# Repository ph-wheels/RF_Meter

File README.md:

# RF_Meter
dual channel rf meter (work in progress)

This project started off with a question concerning replacement or source for
suitable detector diodes for the Boonton RF Millivolt meter quite a few months ago.
As a result of that, the idea was born to create a millivolt and/or power meter
using one of the modern ADC chips available today and since that time a few test
drawning and PCB where used in the process to the current V5 of the ADC board.
This project has been a combined effort with Jacques (ve2azx, http://www.ve2azx.net),
who already had developped a replacement board for the Boonton series of millivolt/
power meter as to fixed the issue with the mechanical chopper, without his valued
contribution, experiance, feedback and high precision RF measurement this project
would never exist.

The current design is based to 2 main PCB's and a battery board which also provides
some shielding to ADC board when mounted on top off it.

The control board consist of a connection to battery board, a flatcable connection
to ADC board and uart connection (ttl level) to external usb serial interface.
The board has and ESP32 MCU chip, which can be flashed via the USB serial interface,
will display info on the LCD screen (3.5" 480x240), monitors changes of the rotary
switch, touch screen, on-board push buttons and read/controls behaviour of the ADC
board. The RF Meter is battery powered and should be capable to provide adequate power
for several hours from 2x 2000 mAh or larger capacity batteries, optional board space
is provided to house a BMS unit and can be charged by the 2S 1A battery charger module
or via a barrel jack socket to deliver power via on-board regulator (3V3) to the MCU and
LCD screen.

The ADC board consist of 2 SMA and a flatcable connection to the control board,
optionally a connection to a 2 pin Amphenol connector, simular to the Boonton instruments.
This board holds 3 main area's being 3x input circuit, multiplexer with the ADC chip and the
voltages / reference sources with some control to switch attenuator and optional panel leds.
The input circuits for channels A/B are terminated with 50 Ohm followed by detector circuit
and attenuator, which is used to obtain a +23dBm range, into a differential low noise x1
amplifier, channel C (with it's components populated) only has the differential 5M6 resistors, the
attenuator and differential low noise x1 amplifier and is therefore not be a 50 Ohm input source.

Project status has been closed for now as we have finished our mean development goals being:
- a battery powered, using modern chips with large enough display making it a usable instrument
- a less than -55 dBm and up to +23 dBm input range
- a frequency range of less then 10 MHz upto in excess of 1 GHz
- an auto range mechanism in place over entire input range
- mechanism in place to load and maintain correction tables in none volatile memory

One area left for improvement is the option to obtain differential power reading between channel
B - A which kind of works (reasonably well within the lower 2 ranges) but will be slower in it's
update frequency then we expected it to be.

Future plans currently don't exist other then having an update schematic in place base on a dual
ADC chip approach which will speedup the channel B - A mode by factor 2x to 3x BUT this will yield
into a higher build cost due to extra ADC and the SSR / Mux chip.

Suggestion as how to build can be found in due time in folder 'Build' which will provide info and
steps to build the ADC and Control board and best practice to test and put each board into operation.

Paul	(PE1FCB (ex))

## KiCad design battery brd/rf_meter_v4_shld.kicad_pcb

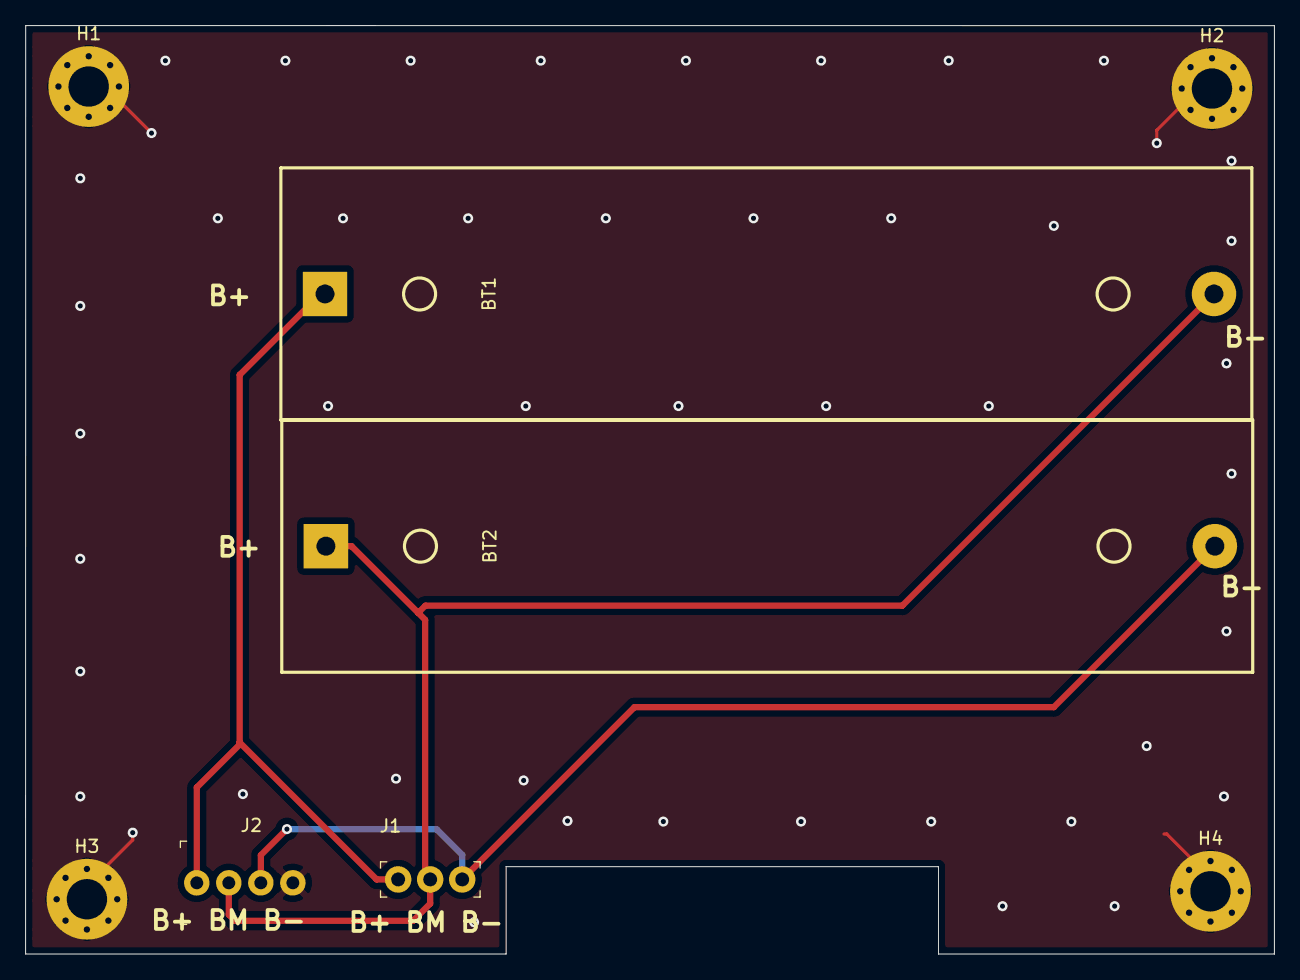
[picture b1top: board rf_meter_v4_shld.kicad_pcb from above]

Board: 2 copper layers, 99.0 x 73.6 mm, 8 parts (0 on the bottom side), 4 nets.

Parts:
BT1, BT2: Li-Ion 18650; Battery_Holder_2S
H1, H2, H3, H4: MountingHole; MountingHole_3.2mm_M3_Pad_Via
J1: Bat_Cntrl; PinHeader_1x3_P2.54_Drill1.1mm
J2: Bat_Test; PinHeader_1x4_P2.54mm_Drill1.02mm

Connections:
GND: H1.1, H2.1, H3.1, H4.1, J2.4
unnamed: BT1.1, J1.1, J2.1
unnamed: BT1.2, BT2.1, J1.2, J2.2
unnamed: BT2.2, J1.3, J2.3

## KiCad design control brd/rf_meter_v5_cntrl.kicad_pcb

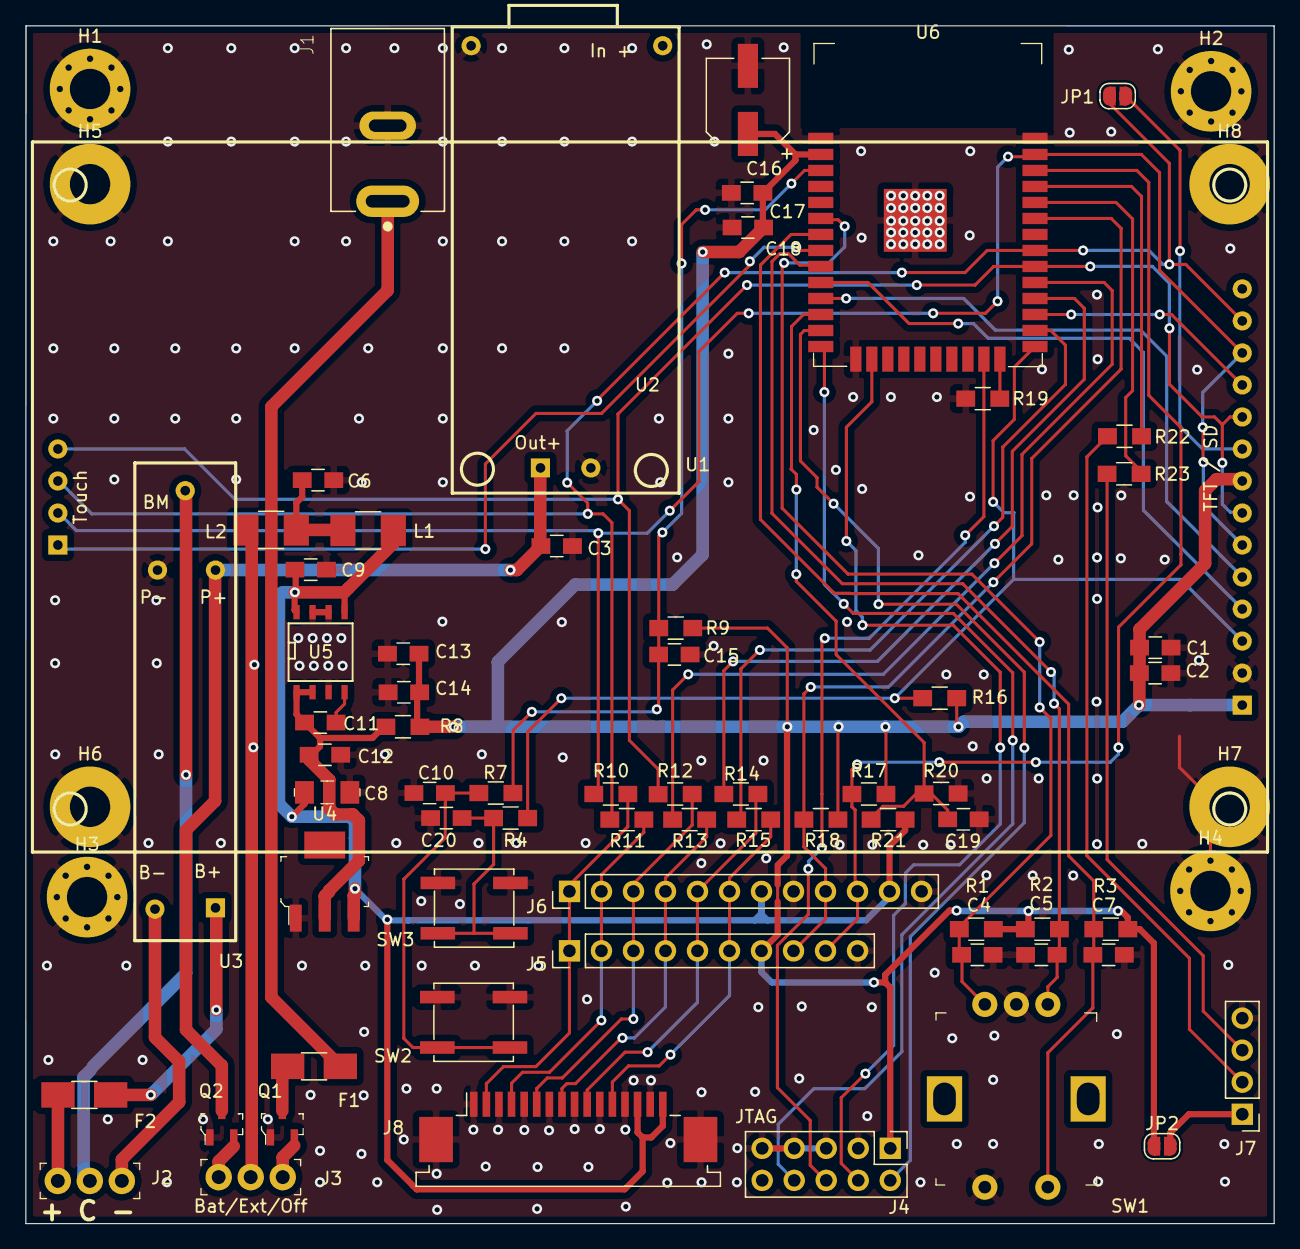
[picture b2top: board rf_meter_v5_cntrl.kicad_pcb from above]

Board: 2 copper layers, 99.0 x 95.0 mm, 74 parts (0 on the bottom side), 53 nets.

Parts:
C1, C9, C13, C18: 0.1; C_0805_HandSoldering
C2, C6, C12, C14, C17: 10u; C_0805_HandSoldering
C3: 10uF; C_0805_HandSoldering
C4, C5, C7, C11: 10n; C_0805_HandSoldering
C8: 47u; 1206
C10, C15, C19, C20: 1n; C_0805_HandSoldering
C16: 100u; CP_Elec_6.3x5.7
F1: Polyfuse_.5A; Fuse_SMD1206_HandSoldering
F2: Polyfuse_1A; Fuse_SMD1206_HandSoldering
H1, H2, H3, H4: MH; MountingHole_3.2mm_M3_Pad_Via
H5, H6, H7, H8: MH; MountingHole_3.2mm_M3_Pad
J1: PJ-037A; CUI_PJ-037A
J2: Bat 2S Li-Ion; PinHeader_1x3_P2.54_Drill1.1mm
J3: Bat/Ext/Off; PinHeader_1x3_P2.54_Drill1.1mm
J4: JTAG; Pin_Header_Straight_2x05_Pitch2.54mm
J5: Logic Test; Pin_Header_Straight_1x10_Pitch2.54mm
J6: RF_Brd; Pin_Header_Straight_1x12_Pitch2.54mm
J7: Uart; Pin_Header_Straight_1x04_Pitch2.54mm
J8: FFC MCU Interface; TE_1-84952-6_1x16-1MP_P1.0mm_Horizontal
JP1: SDO En; SolderJumper-2_P1.3mm_Open_RoundedPad1.0x1.5mm
JP2: 3V3 Pwr; SolderJumper-2_P1.3mm_Open_RoundedPad1.0x1.5mm
L1, L2: 8.4 mH; L_1210_HandSoldering
Q1, Q2: IRF6402; SOT-23-3
R1, R2, R3, R17, R18: 4K7; R_0805_HandSoldering
R4, R7: 470; R_0805_HandSoldering
R8, R22, R23: 0; R_0805_HandSoldering
R9: 12K; R_0805_HandSoldering
R10, R11, R12, R13, R14, R15: 33; R_0805_HandSoldering
R16, R19: NC; R_0805_HandSoldering
R20: 10K; R_0805_HandSoldering
R21: 27K; R_0805_HandSoldering
SW1: Encoder_Switch; Rotary_Encoder_Switched_PEC11R
SW2: Reset; SW_SPST_EVPBF
SW3: Boot; SW_SPST_EVPBF
U1: USB_C_Charge_2S; USB-C_Charge_2S
U2: MSP2807; 3.5_TFT
U3: BMS_Li-Ion; HX-2S-A10
U4: AMS1117-3.3; SOT-223-4
U5: LT1763-3V3; SOIC-8-N
U6: ESP32-WROOM-32; ESP32-WROOM-32D

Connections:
CS_0: R13.1, U6.29
CS_1: R4.1, R16.2, U2.3, U6.25
CS_2: U2.11, U6.27
CS_3: U2.4_1, U6.8
CS_4: J4.6, U6.23
DC: U2.5, U6.11
EN: C15.1, R7.1, R9.2, U6.3
GND: C1.2, C2.2, C3.2, C4.2, C5.2, C6.2, C7.2, C8.2, C9.2, C10.2, C12.2, C13.2, C14.2, C15.2, C16.2, C17.2, C18.2, C19.2, C20.2, H1.1, H2.1, H3.1, H4.1, H5.1, H6.1, H7.1, H8.1, J1.2, J4.3, J4.5, J4.7, J4.9, J5.10, J6.8, J6.12, J7.4, J8.1, J8.3, J8.5, J8.7, J8.9, J8.11, J8.13, J8.15, J8.MP, Q1.1, Q2.1, R19.2, R20.2, SW1.2, SW1.C, SW2.1, SW3.1, U1.2, U1.3, U2.2, U3.5, U4.1, U5.3, U5.6, U5.7, U6.1, U6.15, U6.38, U6.39
H_MISO: J4.8, U6.14
H_MOSI: J4.4, U6.16
H_SCK: J4.2, U6.13
MCU_3V3: C1.1, C2.1, C13.1, C14.1, C16.1, C17.1, C18.1, J4.1, J5.7, JP2.1, R1.1, R2.1, R3.1, R8.1, R9.1, R16.1, R17.1, R18.1, U2.1, U2.8, U6.2
unnamed: C3.1, Q2.3, U1.1, U3.4
unnamed: C6.1, L1.2, L2.1
unnamed: C10.1, R7.2, SW2.2
unnamed: C11.1, C12.1, R8.2, U4.2, U5.1, U5.2
unnamed: C11.2, U5.4
unnamed: C19.1, R20.1, R21.2, U6.12
unnamed: C20.1, R4.2, SW3.2
unnamed: F1.1, Q1.3
unnamed: F1.2, J1.1
unnamed: F2.1, J2.1
unnamed: F2.2, U3.1
unnamed: J2.2, U3.2
unnamed: J2.3, U3.3
unnamed: J3.1, Q2.2
unnamed: J3.2, L2.2
unnamed: J3.3, Q1.2
unnamed: J5.1, J6.1, J8.2, R10.2
unnamed: J5.2, J6.2, J8.4, R11.2
unnamed: J5.3, J6.3, J8.6, R12.2
unnamed: J5.4, J6.4, J8.8, R13.2
unnamed: J5.5, J6.5, J8.10, R14.2
unnamed: J5.6, J6.6, J8.12, R15.2
unnamed: J7.1, JP2.2
unnamed: J7.2, R22.1
unnamed: J7.3, R23.1
unnamed: JP1.1, U2.9
unnamed: R19.1, U6.24
unnamed: R22.2, U6.35
unnamed: R23.2, U6.34
RST: U2.4, U6.10
SCL: J5.9, J6.10, R17.2, U6.36
SDA: J5.8, J6.9, R18.2, U6.33
SWA: C5.1, R2.2, SW1.A, U6.9
SWB: C4.1, R1.2, SW1.B, U6.6
SWC: C7.1, R3.2, SW1.1, U6.7
SYNC: R14.1, U6.28
V_Ana: C8.1, C9.1, J6.7, J6.11, J8.14, J8.16, L1.1, R21.1, U4.3, U5.5, U5.8
V_MISO: JP1.2, R11.1, U2.4_3, U2.13, U6.31
V_MOSI: R10.1, U2.4_2, U2.6, U2.12, U6.37
V_SCK: R12.1, U2.4_4, U2.7, U2.10, U6.30
~RDY: R15.1, U6.26

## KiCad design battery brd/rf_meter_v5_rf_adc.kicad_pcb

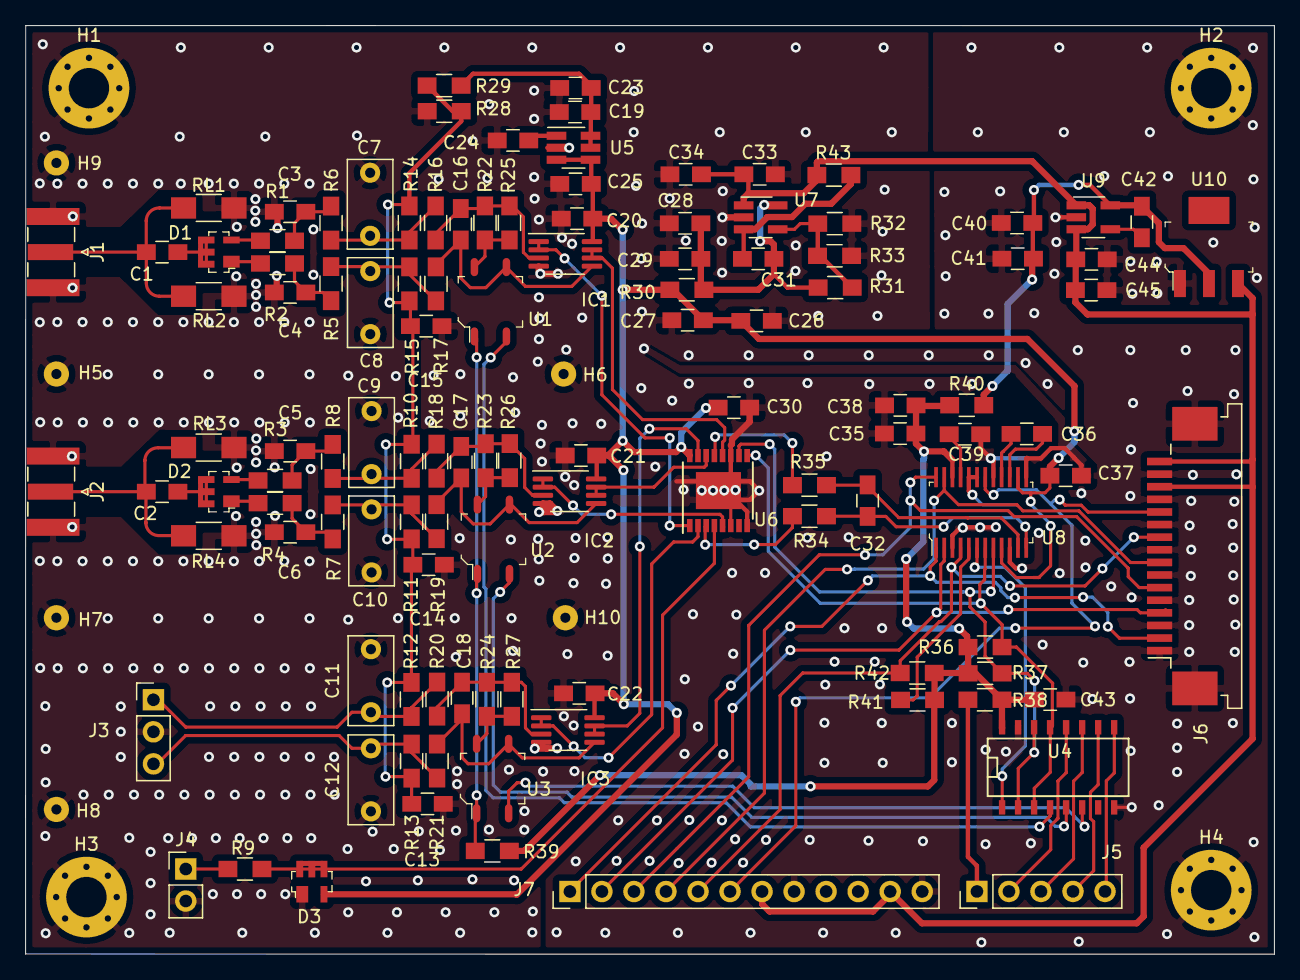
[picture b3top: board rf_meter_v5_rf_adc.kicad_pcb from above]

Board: 2 copper layers, 99.0 x 73.6 mm, 125 parts (0 on the bottom side), 73 nets.

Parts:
C1, C3, C4: 1n; C_0805_HandSoldering
C2, C5, C6: 1nF; C_0805_HandSoldering
C7, C8, C9, C10, C11, C12: 47n; C_Rect_L7.0mm_W3.5mm_P5.00mm
C13, C19, C20, C21, C22, C24, C25, C26, C28, C32, C33, C35, C36, C37, C40, C43, C44: 100n; C_0805_HandSoldering
C14, C15: 100nF; C_0805_HandSoldering
C16, C17, C18: 10n; C_0805_HandSoldering
C23, C27, C34, C38, C45: 10u; C_0805_HandSoldering
C29, C41: 4u7; C_0805_HandSoldering
C30: 0.1; C_0805_HandSoldering
C31, C42: 10nF; C_0805_HandSoldering
C39: 1u; C_0805_HandSoldering
D1, D2, D3: BAT62; SOT-143-4-SPC
H1, H2, H3, H4: MH; MountingHole_3.2mm_M3_Pad_Via
H5, H6, H7, H8, H9, H10: MH; SolderWirePad_single_0-8mmDrill
IC1, IC2, IC3: LTC2055; MSOP-8_3x3mm_P0.65mm
J1, J2: SMA; SMA_Samtec_SMA-J-P-X-ST-EM1_EdgeMount
J3: Amphenol 80-PC2F; Pin_Header_Straight_1x03_Pitch2.54mm
J4: Vtest; Pin_Header_Straight_1x02_Pitch2.54mm
J5: Panel Leds; Pin_Header_Straight_1x05_Pitch2.54mm
J6: FFC MCU Interface; TE_1-84952-6_1x16-1MP_P1.0mm_Horizontal
J7: MCU interface; Pin_Header_Straight_1x12_Pitch2.54mm
R1, R2, R3, R4: 110; R_0805_HandSoldering
R5, R6, R7, R8: 560; R_0805_HandSoldering
R9, R29, R34, R35: 1K; R_0805_HandSoldering
R10, R11, R12, R13, R14, R15: 5M6; R_0805_HandSoldering
R16, R17, R18, R19, R20, R21, R22, R23, R24, R25, R26, R27: 100K; R_0805_HandSoldering
R28: R_0805_HandSoldering
R30, R40, R43: 0; R_0805_HandSoldering
R31, R41, R42: 10K; R_0805_HandSoldering
R32: 20K; R_0805_HandSoldering
R33: 6K8; R_0805_HandSoldering
R36, R37: 4K7; R_0805_HandSoldering
R38, R39: 270; R_0805_HandSoldering
RL1, RL2: R_1206_HandSoldering
RL3, RL4: 100; R_1206_HandSoldering
U1, U2, U3: AQY212; SOP-4_W3.81mm
U4: 74LVC139; SO-16-N
U5: MAX6070 - 1V8; SOT-23-6_Handsoldering
U6: MAX4618; TSSOP-16-1EP_4.4x5mm_P0.65mm
U7: LT1761-BYP; SOT-23-5_HandSoldering
U8: MAX11270; TSSOP-24_W4.40mm
U9: LT1761-3.3; SOT-23-5_HandSoldering
U10: AMS1117-3.3; SOT-223-4

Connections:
AV3V6DD: C20.1, C21.1, C22.1, C25.1, C26.1, C27.1, C30.1, C37.1, D3.2, IC1.8, IC2.8, IC3.8, R30.1, U5.3, U5.4, U6.16, U8.9, U8.14
Att_A: U1.2, U4.4
Att_B: U2.2, U4.5
Att_C: U3.2, U4.6
Att_Ena: U4.1, U8.6
D3V3DD: C35.1, C38.1, C43.1, R36.1, R37.1, R38.1, R39.1, R40.1, R41.2, R42.2, U4.16, U8.22
D3V3LED: J5.1, R38.2
D3V3R: R39.2, U1.1, U2.1, U3.1
D7VDD: C33.1, C34.1, C44.1, C45.1, J6.14, J6.16, J7.7, J7.11, R43.2, U7.1, U9.1, U9.3, U10.3
GND: C3.2, C4.1, C5.2, C6.1, C7.2, C8.1, C9.2, C10.1, C11.2, C12.1, C13.2, C14.2, C15.2, C19.2, C20.2, C21.2, C22.2, C23.2, C24.2, C25.2, C26.2, C27.2, C28.2, C29.2, C30.2, C33.2, C34.2, C35.2, C37.2, C38.2, C39.2, C40.2, C41.2, C43.2, C44.2, C45.2, D3.1, H1.1, H2.1, H3.1, H4.1, H5.1, H6.1, H7.1, H8.1, H9.1, H10.1, IC1.4, IC2.4, IC3.4, J1.2, J2.2, J3.2, J4.2, J6.1, J6.3, J6.5, J6.7, J6.9, J6.11, J6.13, J6.15, J6.MP, J7.8, J7.12, R28.1, R32.1, R33.1, RL1.1, RL2.2, RL3.1, RL4.2, U4.8, U4.15, U5.2, U6.6, U6.8, U6.11, U6.17, U7.2, U8.3, U8.10, U8.13, U8.17, U8.19, U8.20, U9.2, U10.1
unnamed: C1.1, D1.3
unnamed: C1.2, J1.1, RL1.2, RL2.1
unnamed: C2.1, D2.3
unnamed: C2.2, J2.1, RL3.2, RL4.1
unnamed: C3.1, R1.2, R6.1
unnamed: C4.2, R2.2, R5.1
unnamed: C5.1, R3.2, R8.1
unnamed: C6.2, R4.2, R7.1
unnamed: C7.1, R6.2, R14.1, R16.1
unnamed: C8.2, R5.2, R15.2, R17.1
unnamed: C9.1, R8.2, R10.1, R18.1
unnamed: C10.2, R7.2, R11.2, R19.1
unnamed: C11.1, J3.1, R12.1, R20.1
unnamed: C12.2, J3.3, R13.2, R21.1
unnamed: C16.1, IC1.3, R16.2, R22.1, R25.1
unnamed: C16.2, IC1.5, R17.2, U1.3
unnamed: C17.1, IC2.3, R18.2, R23.1, R26.1
unnamed: C17.2, IC2.5, R19.2, U2.3
unnamed: C18.1, IC3.3, R20.2, R24.1, R27.1
unnamed: C18.2, IC3.5, R21.2, U3.3
unnamed: C19.1, C23.1, R29.1, U5.5, U5.6
unnamed: C24.1, U5.1
unnamed: C28.1, C29.1, C31.2, R30.2, R31.1, U7.5
unnamed: C31.1, R43.1, U7.3
unnamed: C32.1, R34.2, U8.12
unnamed: C32.2, R35.2, U8.11
unnamed: C36.1, U8.16
unnamed: C36.2, U8.15
unnamed: C39.1, U8.21
unnamed: C40.1, C41.1, C42.1, R40.2, U9.5, U10.2
unnamed: C42.2, U9.4
unnamed: D1.1, R2.1
unnamed: D1.2, R1.1
unnamed: D2.1, R4.1
unnamed: D2.2, R3.1
unnamed: D3.3, R9.2, U6.4
unnamed: IC1.1, IC1.2, U6.1
unnamed: IC1.6, IC1.7, U6.12
unnamed: IC2.1, IC2.2, U6.5
unnamed: IC2.6, IC2.7, U6.14
unnamed: IC3.1, IC3.2, U6.2
unnamed: IC3.6, IC3.7, U6.15
unnamed: J4.1, R9.1
unnamed: J5.2, U4.12
unnamed: J5.3, U4.11
unnamed: J5.4, U4.10
unnamed: J5.5, U4.9
unnamed: J6.2, J7.1, U8.1
unnamed: J6.4, J7.2, U8.2
unnamed: J6.6, J7.3, U8.24
unnamed: J6.8, J7.4, U8.23
unnamed: J6.10, J7.5, R42.1, U8.4
unnamed: J6.12, J7.6, U8.18
unnamed: R22.2, R25.2, U1.4
unnamed: R23.2, R26.2, U2.4
unnamed: R24.2, R27.2, U3.4
unnamed: R31.2, R32.2, R33.2, U7.4
unnamed: R34.1, U6.3
unnamed: R35.1, U6.13
unnamed: R36.2, U4.3, U4.13, U6.9, U8.7
unnamed: R37.2, U4.2, U4.14, U6.10, U8.8
unnamed: R41.1, U8.5
VPre: C13.1, C14.1, C15.1, R10.2, R11.1, R12.2, R13.1, R14.2, R15.1, R28.2, R29.2

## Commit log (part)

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2023-01-31 Create LICENSE
